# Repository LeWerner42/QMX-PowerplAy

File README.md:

# USB-C PD adapter for QMX + 50W PA

The QMX-PowerplAy is designed to power the [QRP Labs QMX](https://qrp-labs.com/qmx.html) as well as the [50W PA](https://qrp-labs.com/50wpa.html) off a USB PD Powerbank.
Designed for ultimate portability for SOTA / POTA activations, the board can negotiate `15V` or `20V` with `3A` or `5A` for the PA.
A `12V, 5A` switching regulator powers the QMX. Power Negotiation can be selected with simple Jumpers.

## Hardware
### Schematic
The main component is the [AP33771C](https://www.mouser.ch/ProductDetail/Diodes-Incorporated/AP33771CFBZ-13-FA01?qs=2wMNvWM5ZX7JpCFGcPz6nw%3D%3D) which takes care of USB PD negotiations.
Output Voltage and Current can be set through Jumpers `JP1` and `JP2`.
[The Barrel Jack](https://www.mouser.ch/ProductDetail/Wurth-Elektronik/694106301002?qs=a9WhcLg8qCwOEkcI62k5mA%3D%3D) J2 (5.5mm) directly connects to the negotiated power from USB.
J3 (5.5mm) is connected to the stepped-down 12V for supplying the QMX

### Manufacturing
PCBs can be ordered with the gerbers in [fabrication](./powerplay/fabrication).  
The [Component BOM](https://lewerner42.github.io/QMX-PowerplAy/powerplay/bom/ibom.html) [`powerplay/bom/ibom.html`] lists all neccessary components for soldering.
Be aware of Capacitor Voltage ratings (>= 20V) for capacitors connected to USB power.

## Case
The case is entirely 3D printable and files can be accessed in the [Case](./Case) folder.
The `12V` output is labled `QMX` and the USB power (`15V` or `20V`) is labled `PA`.

## Usage
No Substantial Load should be attached to the barrel jacks when powering up.
The QMX and PA can be connected during power-up.
Successfull power negotiation is indicated by LED 2 (`D2`) breathing.
LED 1 (`D1`) indicates if power is present at all.
In case of failiure to negotiate the requested power level either the highest possible negotiated power is present (e.g. `20V`, `3A` even though `100W` were requested) or only `5V` are present on the PA port.
The step-down (`12V` output) only works if the USB voltage is `> 12V`.
Jumpers `JP1` and `JP2` can be used to change the negotiated power according to the capabilities of the used supply.
The Power select Jumpers are NOT hot-swappable. Change them only when the device is unconnected.

# Authors
This board has been developed specifically for SOTA and POTA purposes by Pol (HB9IKL) and Lennart (HB9IKK).

# License

This work is licensed under Creative Commons Attribution-ShareAlike 3.0 Unported License. 
(http://creativecommons.org/licenses/by-sa/3.0/)

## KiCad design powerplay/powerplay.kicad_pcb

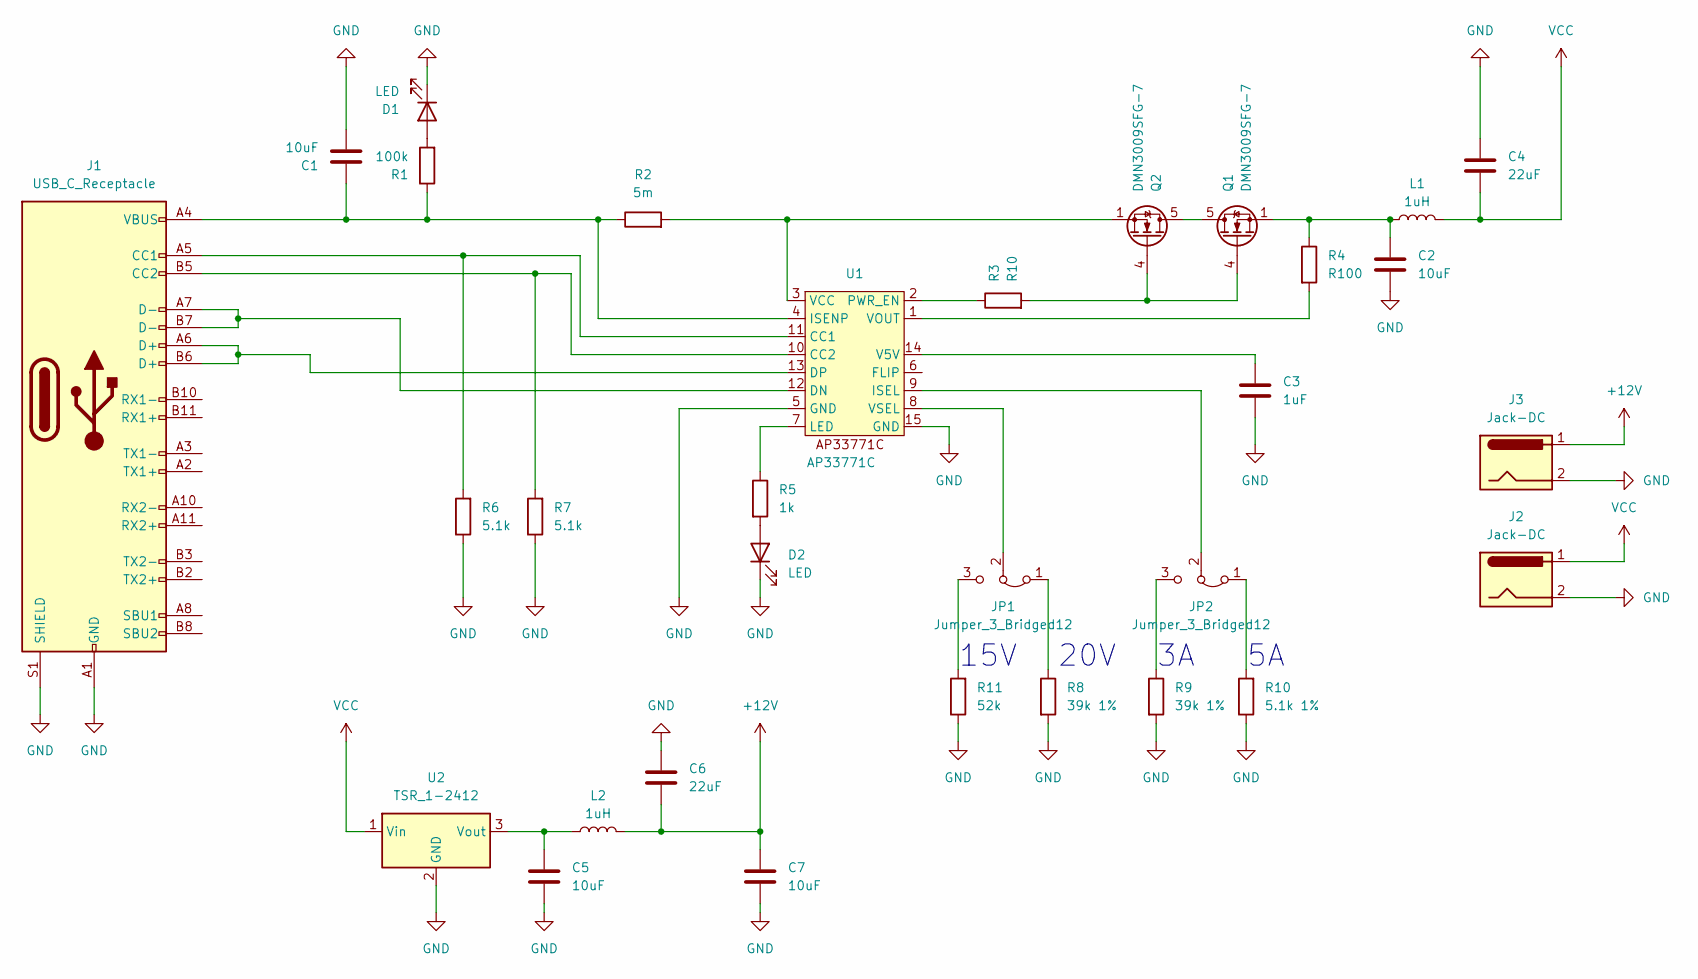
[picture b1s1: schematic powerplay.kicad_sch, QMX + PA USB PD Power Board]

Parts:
C1, C2, C5, C7: 10uF; C_0603_1608Metric
C3: 1uF; C_0603_1608Metric
C4, C6: 22uF; C_0603_1608Metric
D1, D2: LED; LED_0603_1608Metric
J1: USB_C_Receptacle; USB_C_Receptacle_Amphenol_12401610E4-2A
J2, J3: Jack-DC; BarrelJack_Wuerth_6941xx301002
JP1, JP2: Jumper_3_Bridged12; PinHeader_1x03_P2.54mm_Vertical
L1, L2: 1uH; L_Coilcraft_XAL5030-XXX
Q1, Q2: DMN3009SFG-7; Diodes_PowerDI3333-8
R1: 100k; R_0603_1608Metric
R2: 5m; R_2512_6332Metric
R3: R10; R_0603_1608Metric
R4: R100; R_0603_1608Metric
R5: 1k; R_0603_1608Metric
R6, R7: 5.1k; R_0603_1608Metric
R8, R9: 39k 1%; R_0603_1608Metric
R10: 5.1k 1%; R_0603_1608Metric
R11: 52k; R_0603_1608Metric
U1: AP33771C; DFN-14-1EP_3x3mm_P0.4mm_EP1.78x2.35mm
U2: TSR_1-2412; Converter_DCDC_TRACO_TSR-1_THT

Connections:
+12V: C6.2, C7.1, J3.1, L2.2
GND: C1.2, C2.2, C3.2, C4.1, C5.2, C6.1, C7.2, D1.1 (K), D2.1 (K), J1.A1 (GND), J1.A12 (GND), J1.B1 (GND), J1.B12 (GND), J1.S1 (SHIELD), J2.2, J3.2, R6.1, R7.1, R8.2, R9.2, R10.1, R11.1, U1.5 (GND), U1.15 (GND), U2.2 (GND)
unnamed: C2.1, L1.1, Q1.1 (S), Q1.2 (S), Q1.3 (S), R4.1
unnamed: D1.2 (A), R1.2
unnamed: D2.2 (A), R5.2
unnamed: J1.A5 (CC1), R6.2, U1.11 (CC1)
unnamed: J1.B5 (CC2), R7.2, U1.10 (CC2)
unnamed: JP1.1 (A), R8.1
unnamed: JP1.3 (B), R11.2
unnamed: JP1.2 (C), U1.8 (VSEL)
unnamed: JP2.1 (A), R10.2
unnamed: JP2.3 (B), R9.1
unnamed: JP2.2 (C), U1.9 (ISEL)
unnamed: Q1.5 (D), Q2.5 (D)
unnamed: Q1.4 (G), Q2.4 (G), R3.2
unnamed: J1.A7 (D-), J1.B7 (D-), U1.12 (DN)
unnamed: J1.A6 (D+), J1.B6 (D+), U1.13 (DP)
unnamed: C1.1, J1.A4 (VBUS), J1.A9 (VBUS), J1.B4 (VBUS), J1.B9 (VBUS), R1.1, R2.1, U1.4 (ISENP)
unnamed: R5.1, U1.7 (LED)
unnamed: R3.1, U1.2 (PWR_EN)
unnamed: C3.1, U1.14 (V5V)
unnamed: Q2.1 (S), Q2.2 (S), Q2.3 (S), R2.2, U1.3 (VCC)
unnamed: R4.2, U1.1 (VOUT)
unnamed: C5.1, L2.1, U2.3 (Vout)
VCC: C4.2, J2.1, L1.2, U2.1 (Vin)

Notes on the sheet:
20V
15V

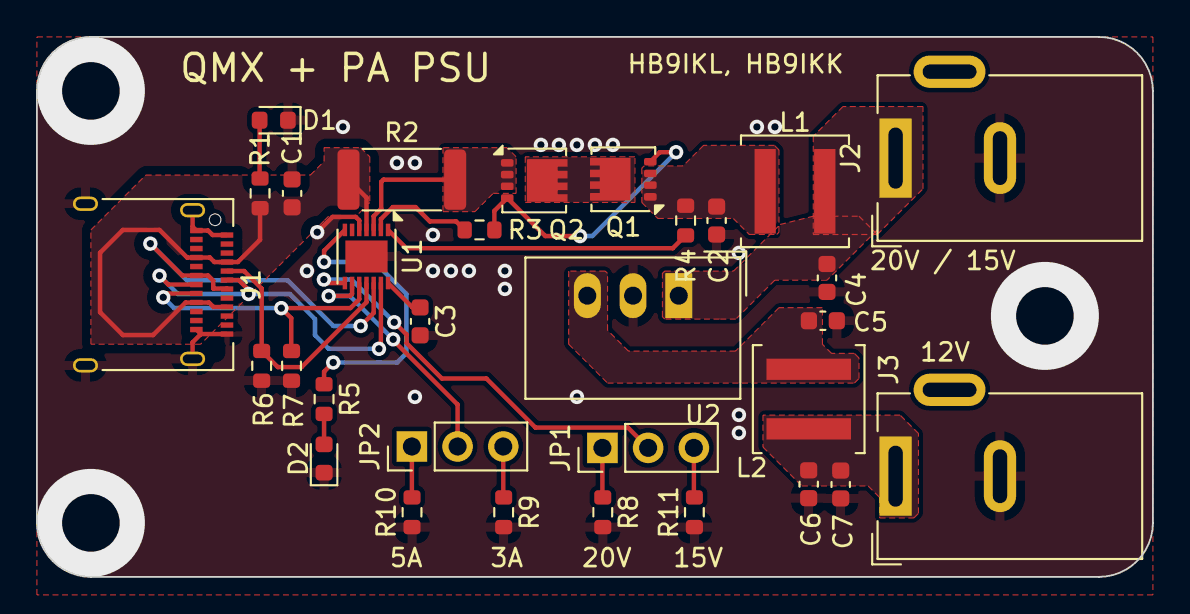
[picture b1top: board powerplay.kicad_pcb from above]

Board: 2 copper layers, 62.0 x 30.0 mm, 31 parts (0 on the bottom side), 25 nets.

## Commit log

2024-10-24 working version
2024-11-18 touchups
2024-11-18 removed lock file
